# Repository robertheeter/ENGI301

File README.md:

# ENGI301
Fall 2023 ENGI 301 Introduction to Practical Electrical Engineering course in the Department of Engineering at Rice University.

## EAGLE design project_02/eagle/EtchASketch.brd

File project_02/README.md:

# **ETCH-A-SKETCH PCB**
- By **[Robert Heeter](https://github.com/robertheeter)**.
- Project completed 15 December 2023 for the ENGI 301 Introduction to Practical Electrical Engineering (Fall 2023) course with Professor Erik Welsh at Rice University.

## **About**
Compact PCB for an Etch-A-Sketch toy using a 2.8" SPI LCD screen, 3 LEDs, 2 potentiometers, 2 buttons, and a PocketBeagle. Created using EAGLE.
- `eagle/`: PCB library, schematic, and board files
- `mfg/`: manufacturing Gerber files
- `docs/`: other documentation and screenshots

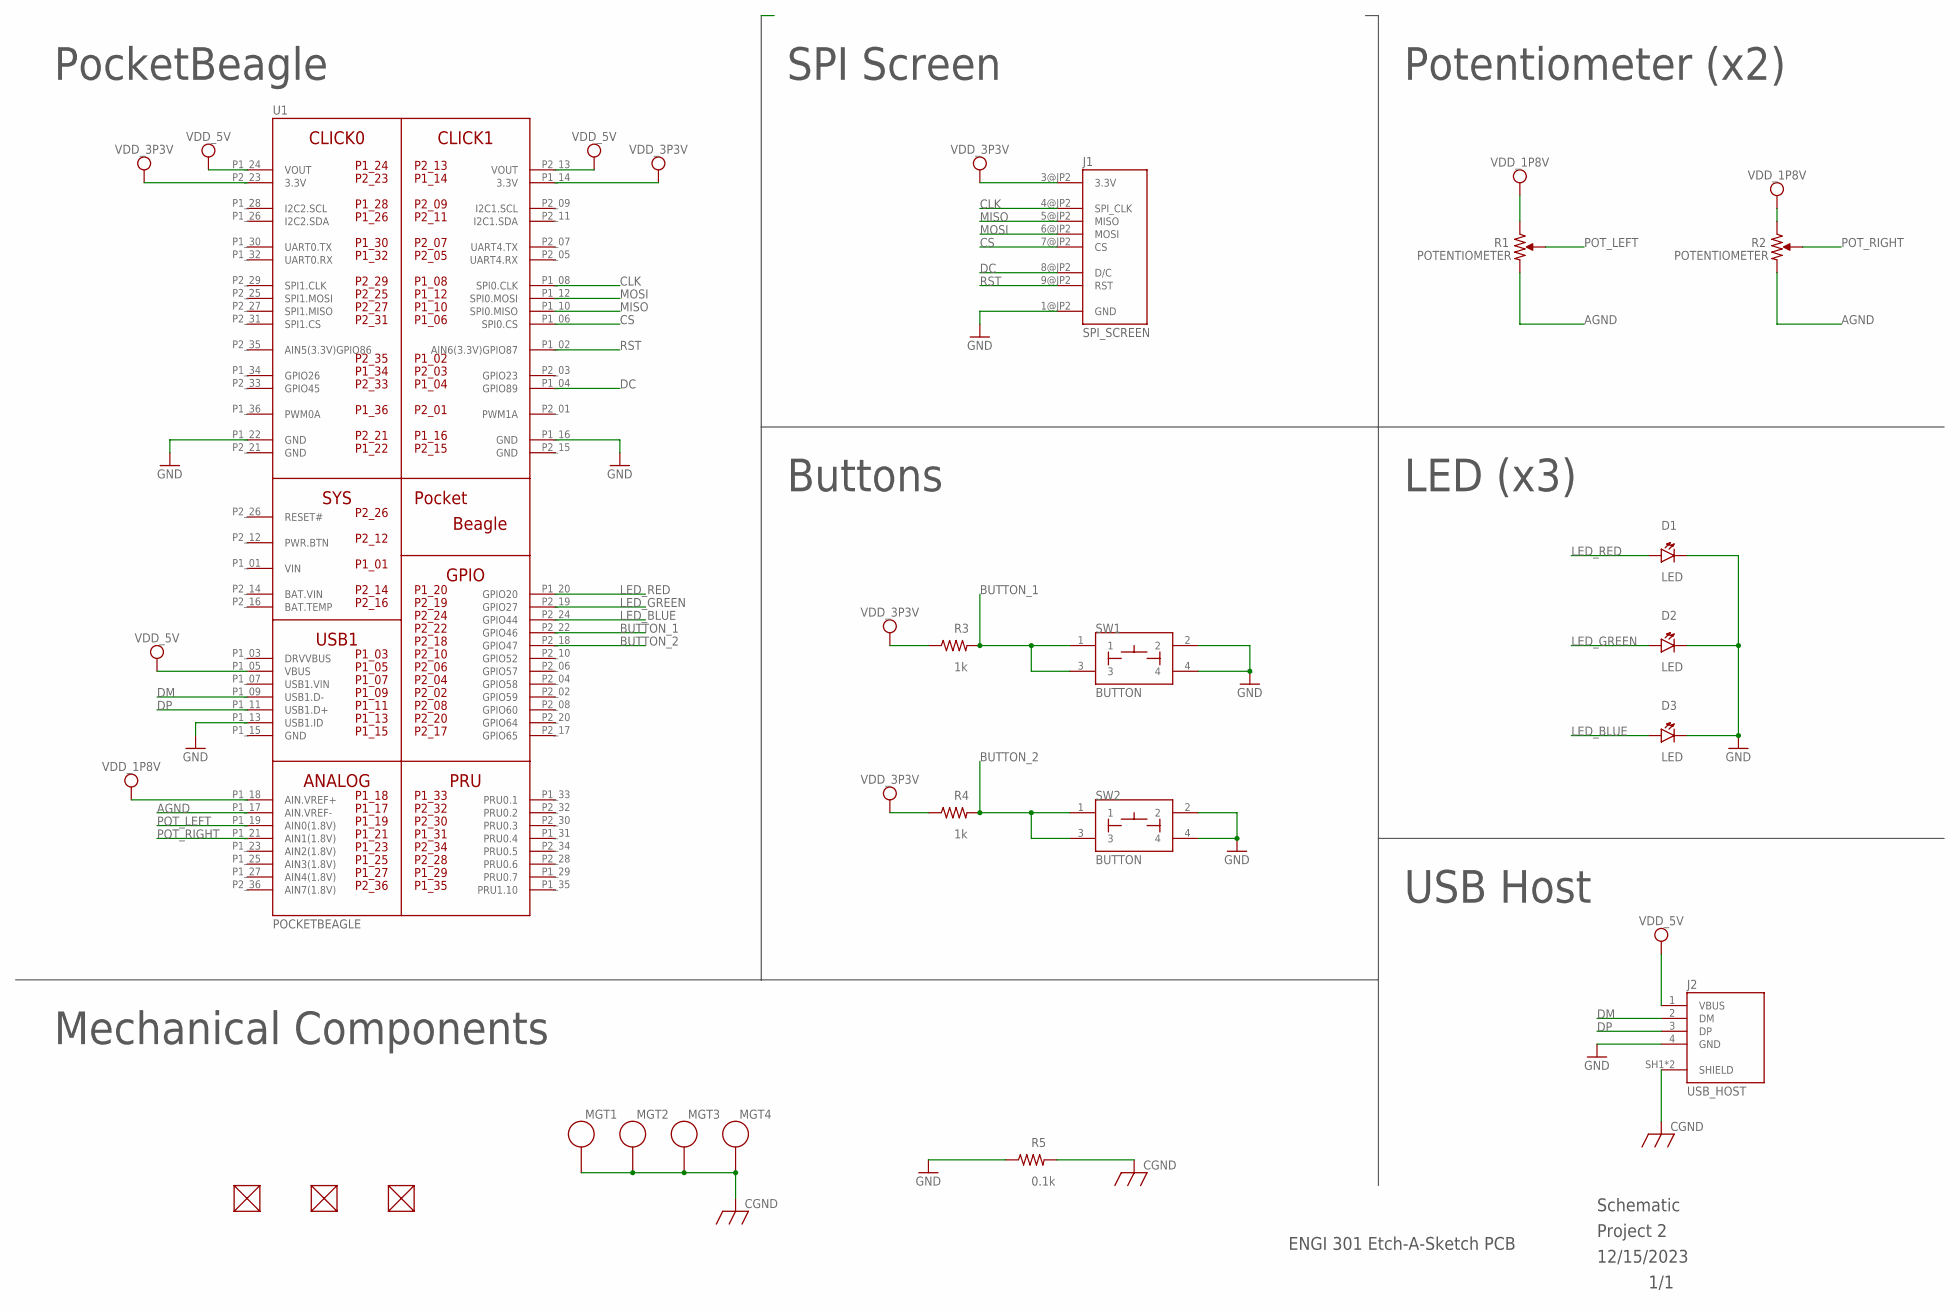
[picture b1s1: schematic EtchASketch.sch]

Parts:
D1, D2, D3: LED; EIA-STD
FUD4, FUD5, FUD6: FIDUCIAL; FIDUCIAL_40MIL
J1: SPI_SCREEN
J2: USB_HOST; USB_TE_292303
MGT1, MGT2, MGT3, MGT4: MOUNTING_HOLE
R1, R2: POTENTIOMETER; POT-PO90S
R3, R4: 1k; R0603
R5: 0.1k; R0603
SW1, SW2: BUTTON; BUTTON_12.5MM
U1: POCKETBEAGLE

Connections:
AGND: R1.CW, R2.CW, U1.P1_17 (AIN.VREF-)
BAT.VIN: U1.P2_14 (BAT.VIN)
BUTTON_1: R3.2, SW1.1, SW1.3, U1.P2_22 (GPIO46)
BUTTON_2: R4.2, SW2.1, SW2.3, U1.P2_18 (GPIO47)
CGND: J2.SH1 (SHIELD), J2.SH2 (SHIELD), MGT1.P$1, MGT2.P$1, MGT3.P$1, MGT4.P$1, R5.2
CLK: J1.4@JP2 (SPI_CLK), U1.P1_08 (SPI0.CLK)
CS: J1.7@JP2 (CS), U1.P1_06 (SPI0.CS)
DC: J1.8@JP2 (D/C), U1.P1_04 (GPIO89)
DM: J2.2 (DM), U1.P1_09 (USB1.D-)
DP: J2.3 (DP), U1.P1_11 (USB1.D+)
GND: D1.CATHODE, D2.CATHODE, D3.CATHODE, J1.1@JP2 (GND), J2.4 (GND), R5.1, SW1.2, SW1.4, SW2.2, SW2.4, U1.P1_13 (USB1.ID), U1.P1_16 (GND), U1.P1_22 (GND), U1.P2_15 (GND), U1.P2_21 (GND)
LED_BLUE: D3.ANODE, U1.P2_24 (GPIO44)
LED_GREEN: D2.ANODE, U1.P2_19 (GPIO27)
LED_RED: D1.ANODE, U1.P1_20 (GPIO20)
MISO: J1.5@JP2 (MISO), U1.P1_10 (SPI0.MISO)
MOSI: J1.6@JP2 (MOSI), U1.P1_12 (SPI0.MOSI)
POT_LEFT: R1.S, U1.P1_19 (AIN0(1.8V))
POT_RIGHT: R2.S, U1.P1_21 (AIN1(1.8V))
RST: J1.9@JP2 (RST), U1.P1_02 (AIN6(3.3V)GPIO87)
VDD_1P8V: R1.CCW, R2.CCW, U1.P1_18 (AIN.VREF+)
VDD_3P3V: J1.3@JP2 (3.3V), R3.1, R4.1, U1.P1_14 (3.3V), U1.P2_23 (3.3V)
VDD_5V: J2.1 (VBUS), U1.P1_05 (VBUS), U1.P1_24 (VOUT), U1.P2_13 (VOUT)
VIN: U1.P1_01 (VIN)

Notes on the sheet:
Buttons
Mechanical Components
PocketBeagle
1/1
ENGI 301 Etch-A-Sketch PCB
Schematic
Project 2
12/15/2023
Potentiometer (x2)
LED (x3)
USB Host
SPI Screen

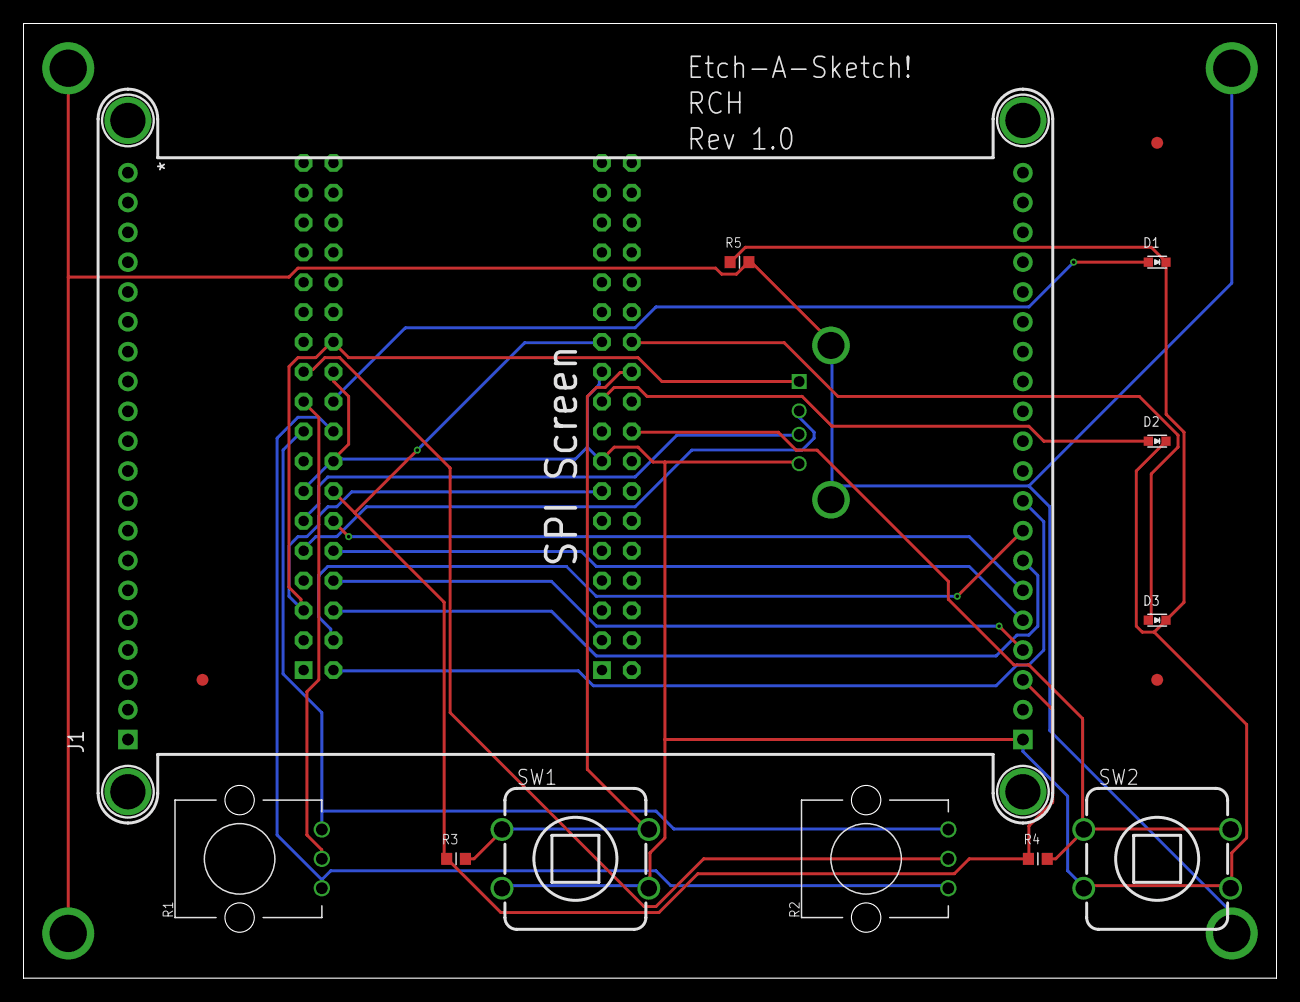
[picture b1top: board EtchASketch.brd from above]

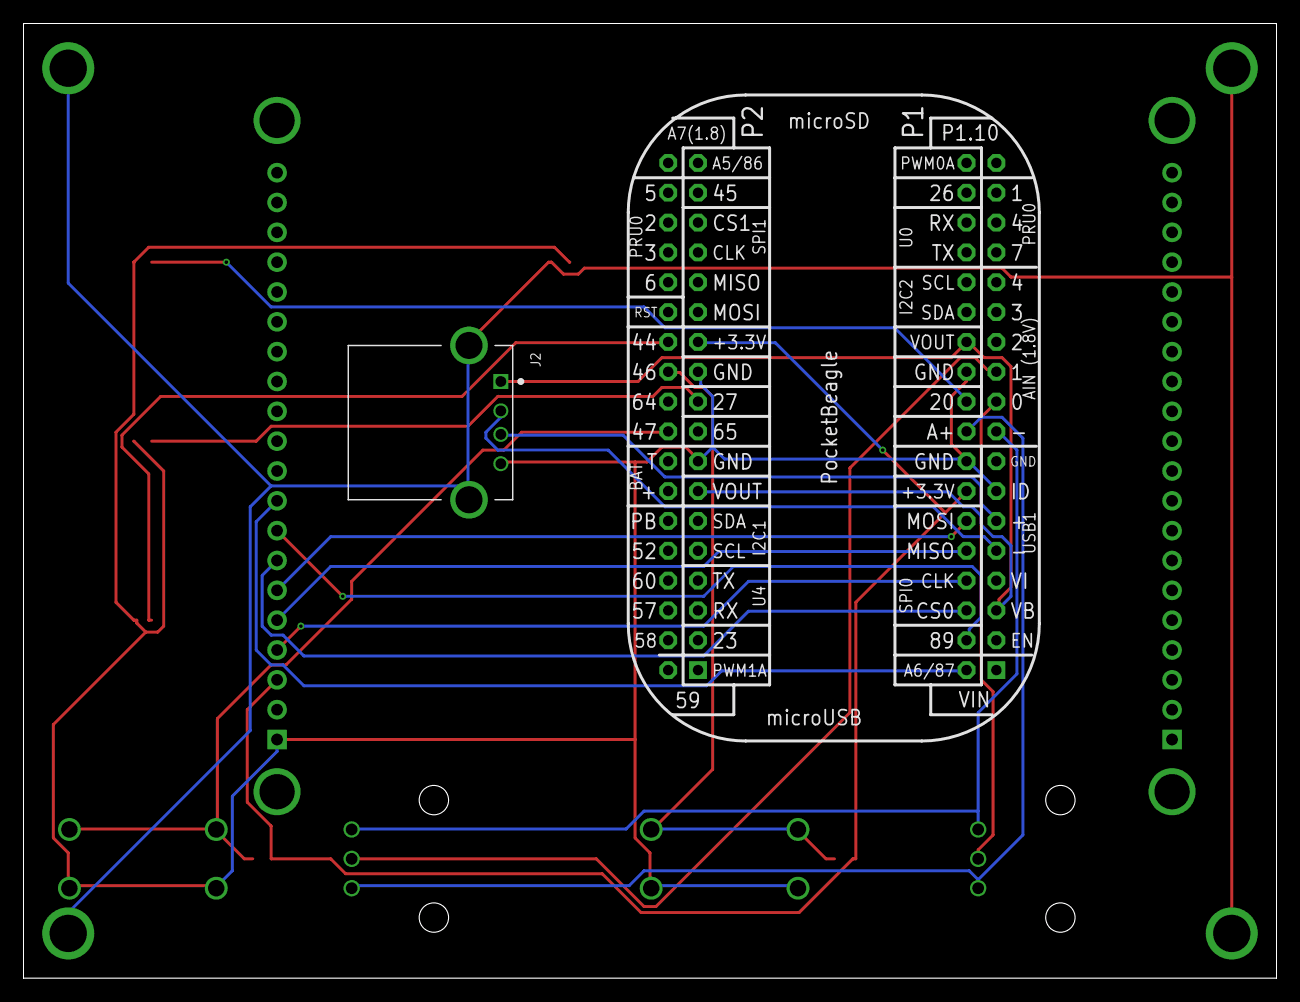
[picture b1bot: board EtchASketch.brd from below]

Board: 4 copper layers, 106.7 x 81.3 mm, 20 parts (2 on the bottom side), 21 nets.

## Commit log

2023-09-26 Create Project 01
2023-09-27 Added HW4-P3 button.py
2023-09-28 Update assignments
2023-10-01 Update proposal
2023-10-13 Add software framework
2023-10-13 Update software framework
2023-11-16 Update docs
2023-12-16 Add project
2023-12-16 Update project
